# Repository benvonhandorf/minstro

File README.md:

# minstro
Remote control head for SDRs using the SoapyRemote server

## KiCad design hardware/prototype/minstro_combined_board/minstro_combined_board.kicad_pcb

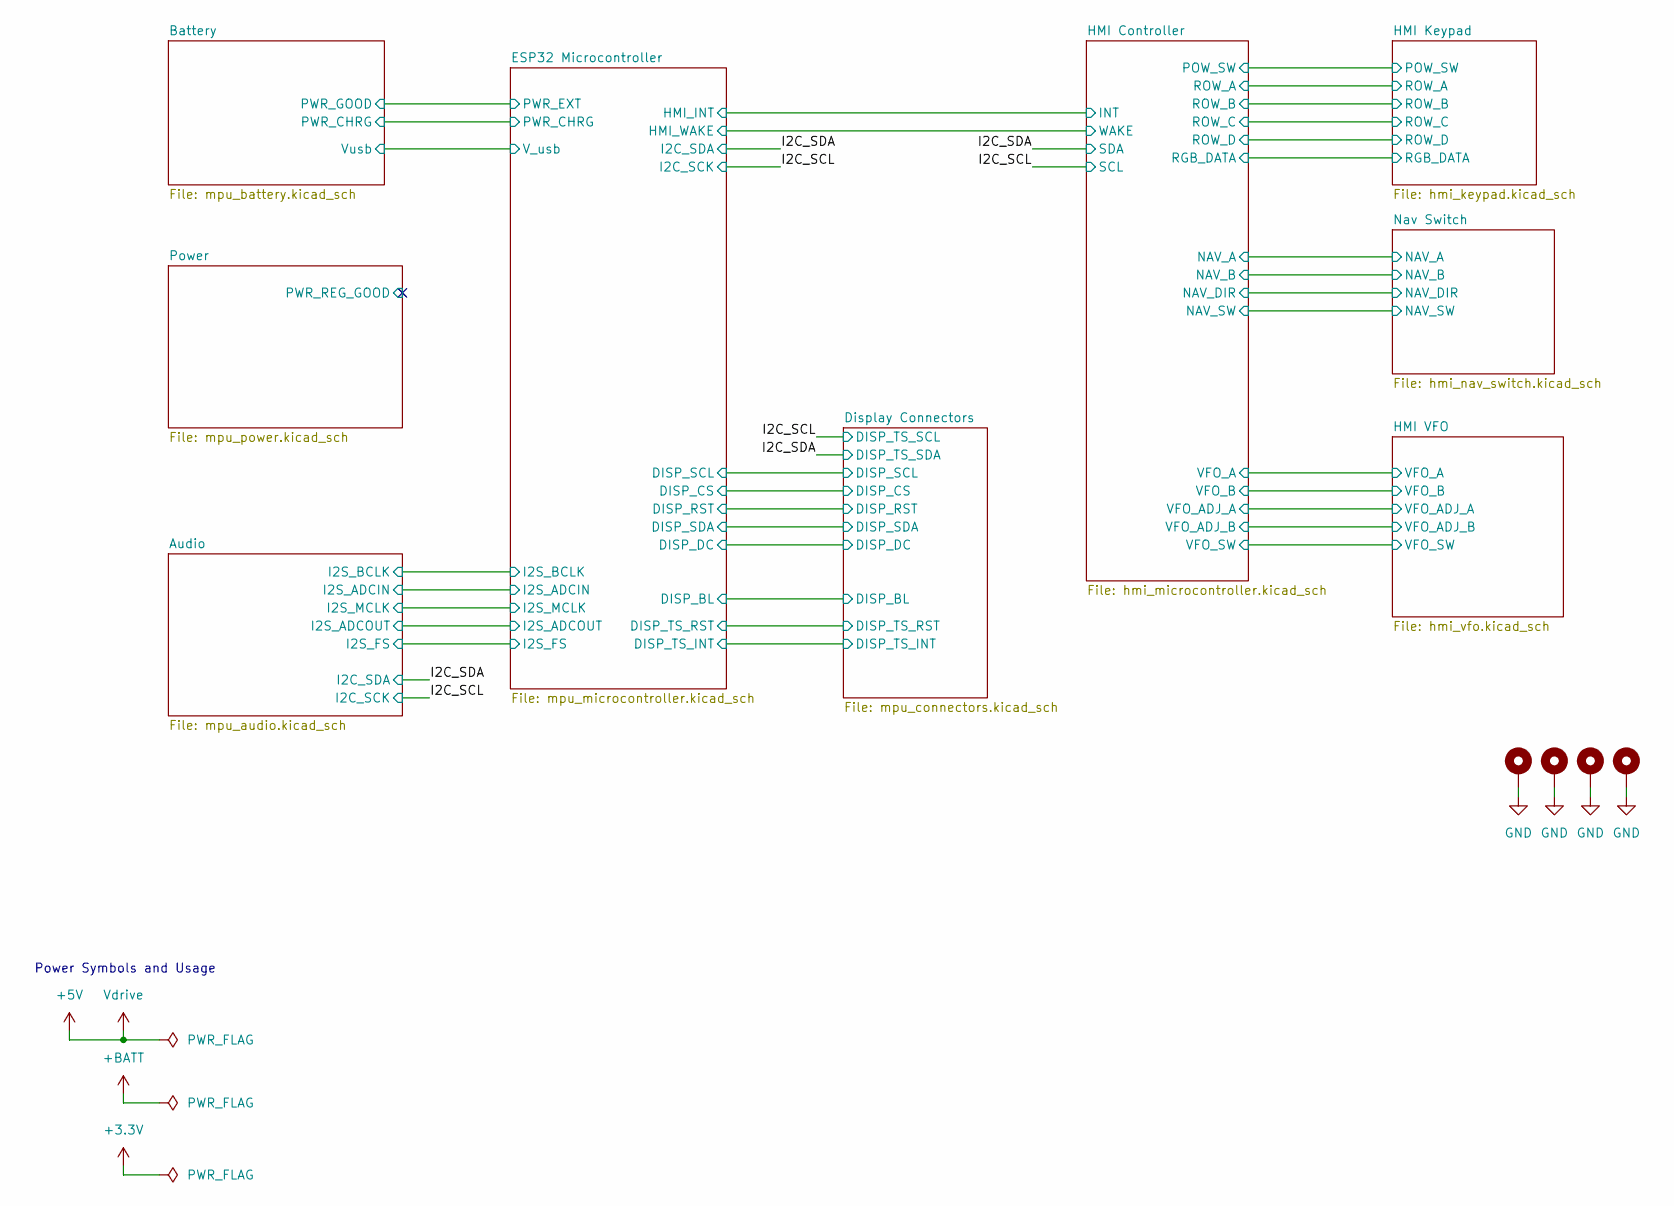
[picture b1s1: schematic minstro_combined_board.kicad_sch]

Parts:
H101, H102, H103, H104: MountingHole_Pad_MP; MountingHole_3.2mm_M3_Pad

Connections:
GND: H101.1, H102.1, H103.1, H104.1; also elsewhere on the board

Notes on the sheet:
Power Symbols and Usage

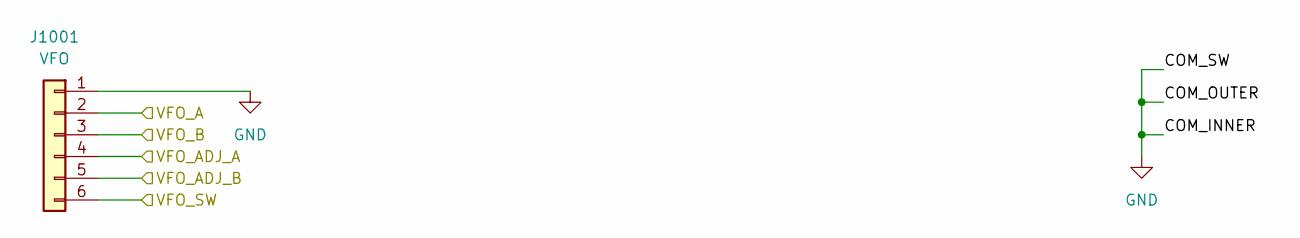
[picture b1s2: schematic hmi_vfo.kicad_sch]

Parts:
J1001: VFO; PinHeader_1x06_P2.54mm_Vertical

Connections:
/HMI Controller/VFO_A: J1001.2; also elsewhere on the board
/HMI Controller/VFO_ADJ_A: J1001.4; also elsewhere on the board
/HMI Controller/VFO_ADJ_B: J1001.5; also elsewhere on the board
/HMI Controller/VFO_B: J1001.3; also elsewhere on the board
/HMI Controller/VFO_SW: J1001.6; also elsewhere on the board
GND: J1001.1; also elsewhere on the board

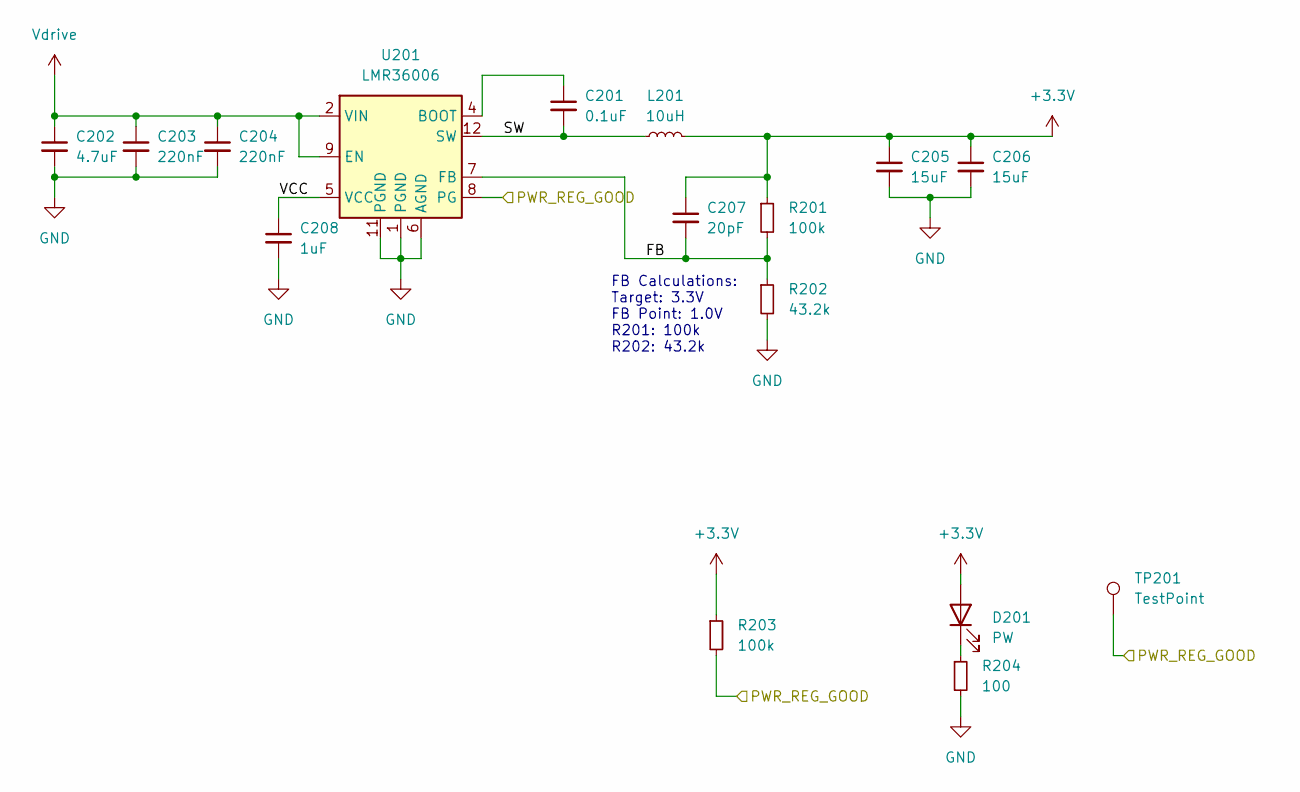
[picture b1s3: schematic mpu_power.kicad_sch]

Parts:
C201: 0.1uF; C_1206_3216Metric
C202: 4.7uF; C_1206_3216Metric
C203, C204: 220nF; C_1206_3216Metric
C205, C206: 15uF; C_1206_3216Metric
C207: 20pF; C_0805_2012Metric
C208: 1uF; C_0805_2012Metric
D201: PW; LED_0805_2012Metric
L201: 10uH; L_Taiyo-Yuden_MD-4040
R201, R203: 100k; R_0603_1608Metric
R202: 43.2k; R_0603_1608Metric
R204: 100; R_0603_1608Metric
TP201: TestPoint; TestPoint_Pad_D1.5mm
U201: LMR36006; LMR36006-VQFN-HR

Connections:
+3.3V: C205.1, C206.1, C207.1, D201.2 (A), L201.2, R201.1, R203.1; also elsewhere on the board
/Power/FB: C207.2, R201.2, R202.1, U201.7 (FB)
/Power/PWR_REG_GOOD: R203.2, TP201.1, U201.8 (PG)
/Power/SW: C201.2, L201.1, U201.3 (SW), U201.12 (SW)
/Power/VCC: C208.1, U201.5 (VCC)
GND: C202.2, C203.2, C204.2, C205.2, C206.2, C208.2, R202.2, R204.2, U201.1 (PGND), U201.6 (AGND), U201.11 (PGND); also elsewhere on the board
unnamed: D201.1 (K), R204.1
unnamed: C201.1, U201.4 (BOOT)

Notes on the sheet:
FB Calculations: Target: 3.3V FB Point: 1.0V R201: 100k R202: 43.2k

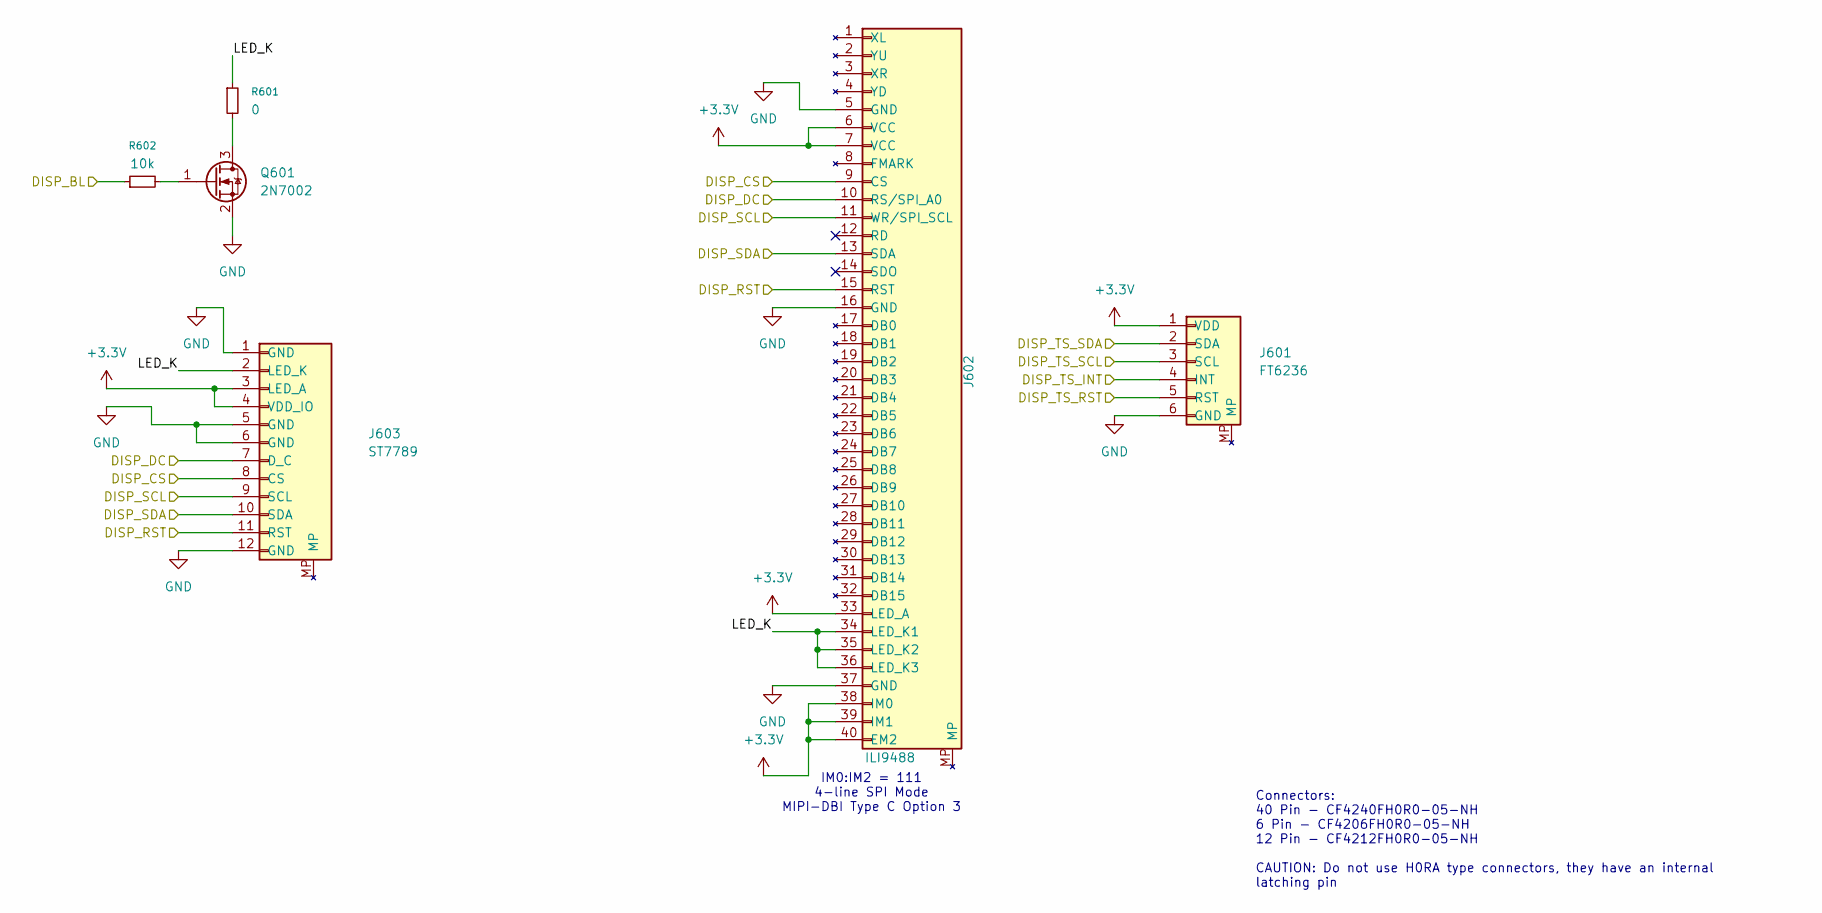
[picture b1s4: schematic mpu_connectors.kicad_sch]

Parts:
J601: FT6236; Cvilux_CF4206FH0R0-05-NH_FFC_01x06-1MP_P0.5mm_Horizontal
J602: ILI9488; Cvilux_CF4240FH0R0-05-NH_FFC_01x40-1MP_P0.5mm_Horizontal
J603: ST7789; Cvilux_CF4212FH0R0-05-NH_FFC_01x12-1MP_P0.5mm_Horizontal_1
Q601: 2N7002; SOT-23
R601: 0; R_0603_1608Metric_Pad0.98x0.95mm_HandSolder
R602: 10k; R_0603_1608Metric_Pad0.98x0.95mm_HandSolder

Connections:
+3.3V: J601.1 (VDD), J602.6 (VCC), J602.7 (VCC), J602.33 (LED_A), J602.38 (IM0), J602.39 (IM1), J602.40 (EM2), J603.3 (LED_A), J603.4 (VDD_IO); also elsewhere on the board
/Display Connectors/DISP_BL: R602.1; also elsewhere on the board
/Display Connectors/DISP_CS: J602.9 (CS), J603.8 (CS); also elsewhere on the board
/Display Connectors/DISP_DC: J602.10 (RS/SPI_A0), J603.7 (D_C); also elsewhere on the board
/Display Connectors/DISP_RST: J602.15 (RST), J603.11 (RST); also elsewhere on the board
/Display Connectors/DISP_SCL: J602.11 (WR/SPI_SCL), J603.9 (SCL); also elsewhere on the board
/Display Connectors/DISP_SDA: J602.13 (SDA), J603.10 (SDA); also elsewhere on the board
/Display Connectors/DISP_TS_INT: J601.4 (INT); also elsewhere on the board
/Display Connectors/DISP_TS_RST: J601.5 (RST); also elsewhere on the board
/Display Connectors/LED_K: J602.34 (LED_K1), J602.35 (LED_K2), J602.36 (LED_K3), J603.2 (LED_K), R601.1
/I2C_SCL: J601.3 (SCL); also elsewhere on the board
/I2C_SDA: J601.2 (SDA); also elsewhere on the board
GND: J601.6 (GND), J602.5 (GND), J602.16 (GND), J602.37 (GND), J603.1 (GND), J603.5 (GND), J603.6 (GND), J603.12 (GND), Q601.2 (S); also elsewhere on the board
unnamed: Q601.3 (D), R601.2
unnamed: Q601.1 (G), R602.2

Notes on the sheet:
IM0:IM2 = 111 4-line SPI Mode MIPI-DBI Type C Option 3
Connectors: 40 Pin - CF4240FH0R0-05-NH 6 Pin - CF4206FH0R0-05-NH 12 Pin - CF4212FH0R0-05-NH CAUTION: Do not use H0RA type connectors, they have an internal latching pin

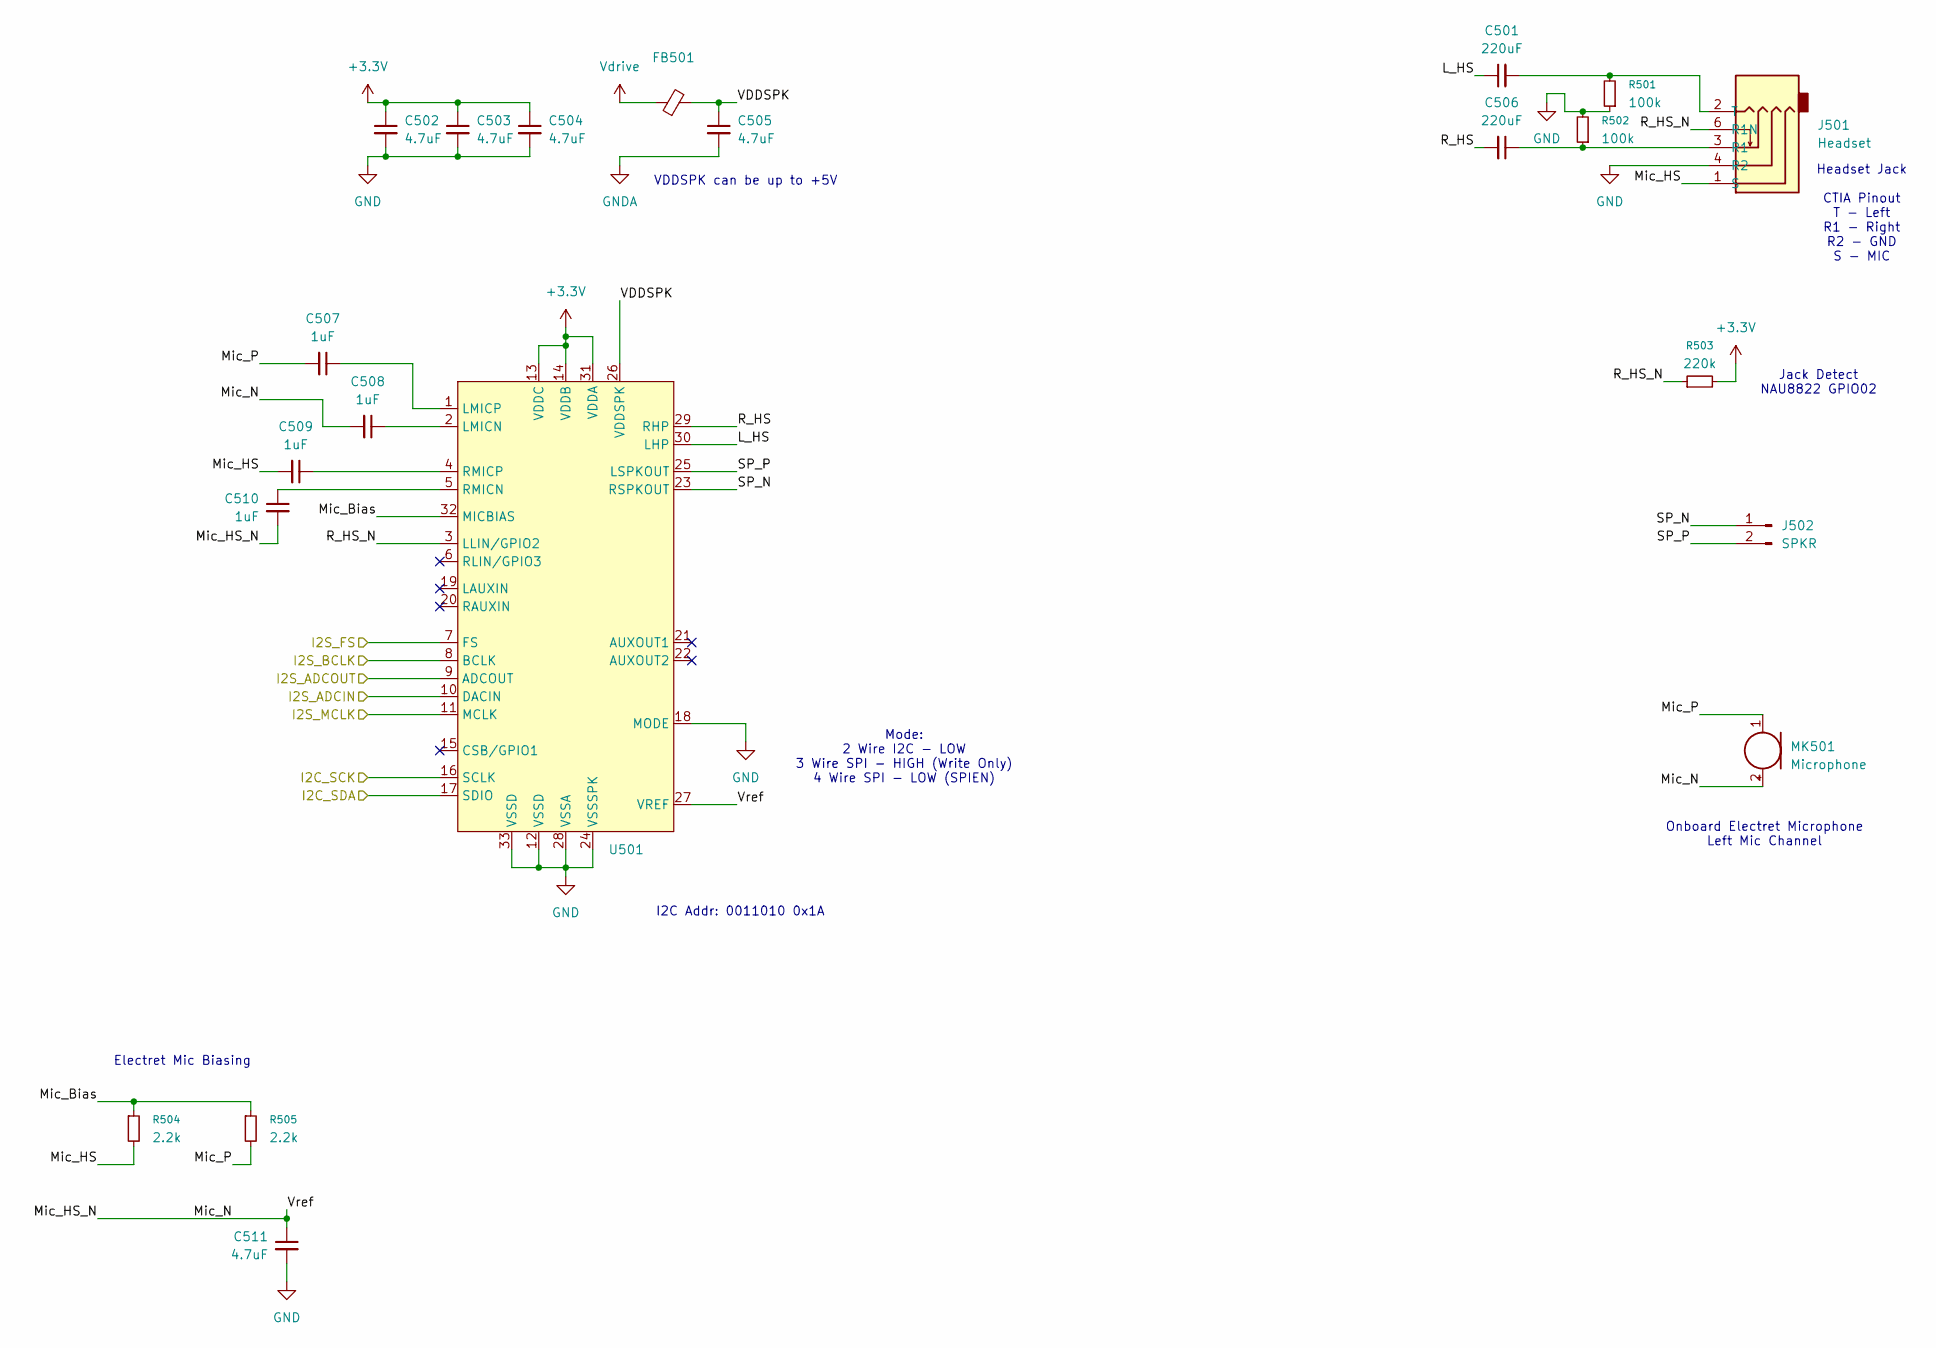
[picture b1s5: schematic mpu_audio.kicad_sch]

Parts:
C501, C506: 220uF; C_1210_3225Metric
C502, C503, C504, C505, C511: 4.7uF; C_0805_2012Metric
C507, C508, C509, C510: 1uF; C_0603_1608Metric
FB501: FerriteBead_Small; R_0805_2012Metric
J501: Headset; SJ-43515RS-SMT-TR
J502: SPKR; JST_ZH_B2B-ZR_1x02_P1.50mm_Vertical
MK501: Microphone; SameSky_CMB-6544PF_Electret_Mic_9.4d
R501, R502: 100k; R_0603_1608Metric
R503: 220k; R_0603_1608Metric
R504, R505: 2.2k; R_0603_1608Metric
U501: QFN-32-1EP_5x5mm_P0.5mm_EP2.7x2.7mm_ThermalVias

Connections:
+3.3V: C502.1, C503.1, C504.1, R503.2, U501.13 (VDDC), U501.14 (VDDB), U501.31 (VDDA); also elsewhere on the board
/Audio/I2S_ADCIN: U501.10 (DACIN); also elsewhere on the board
/Audio/I2S_ADCOUT: U501.9 (ADCOUT); also elsewhere on the board
/Audio/I2S_BCLK: U501.8 (BCLK); also elsewhere on the board
/Audio/I2S_FS: U501.7 (FS); also elsewhere on the board
/Audio/I2S_MCLK: U501.11 (MCLK); also elsewhere on the board
/Audio/L_HS: C501.1, U501.30 (LHP)
/Audio/Mic_Bias: R504.1, R505.1, U501.32 (MICBIAS)
/Audio/Mic_HS: C509.2, J501.1 (S), R504.2
/Audio/Mic_HS_N: C508.2, C510.2, C511.1, MK501.2 (+), U501.27 (VREF)
/Audio/Mic_P: C507.2, MK501.1 (-), R505.2
/Audio/R_HS: C506.2, U501.29 (RHP)
/Audio/R_HS_N: J501.6 (R1N), R503.1, U501.3 (LLIN/GPIO2)
/Audio/SP_N: J502.1, U501.23 (RSPKOUT)
/Audio/SP_P: J502.2, U501.25 (LSPKOUT)
/Audio/VDDSPK: C505.1, FB501.2, U501.26 (VDDSPK)
/I2C_SCL: U501.16 (SCLK); also elsewhere on the board
/I2C_SDA: U501.17 (SDIO); also elsewhere on the board
GND: C502.2, C503.2, C504.2, C511.2, J501.4 (R2), R501.1, R502.2, U501.12 (VSSD), U501.18 (MODE), U501.24 (VSSSPK), U501.28 (VSSA), U501.33 (VSSD); also elsewhere on the board
GNDA: C505.2
unnamed: C506.1, J501.3 (R1), R502.1
unnamed: C501.2, J501.2 (T), R501.2
unnamed: C508.1, U501.2 (LMICN)
unnamed: C507.1, U501.1 (LMICP)
unnamed: C510.1, U501.5 (RMICN)
unnamed: C509.1, U501.4 (RMICP)

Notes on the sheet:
Onboard Electret Microphone Left Mic Channel
VDDSPK can be up to +5V
Electret Mic Biasing
I2C Addr: 0011010 0x1A
Mode: 2 Wire I2C - LOW 3 Wire SPI - HIGH (Write Only) 4 Wire SPI - LOW (SPIEN)
Headset Jack CTIA Pinout T - Left R1 - Right R2 - GND S - MIC
Jack Detect NAU8822 GPIO02

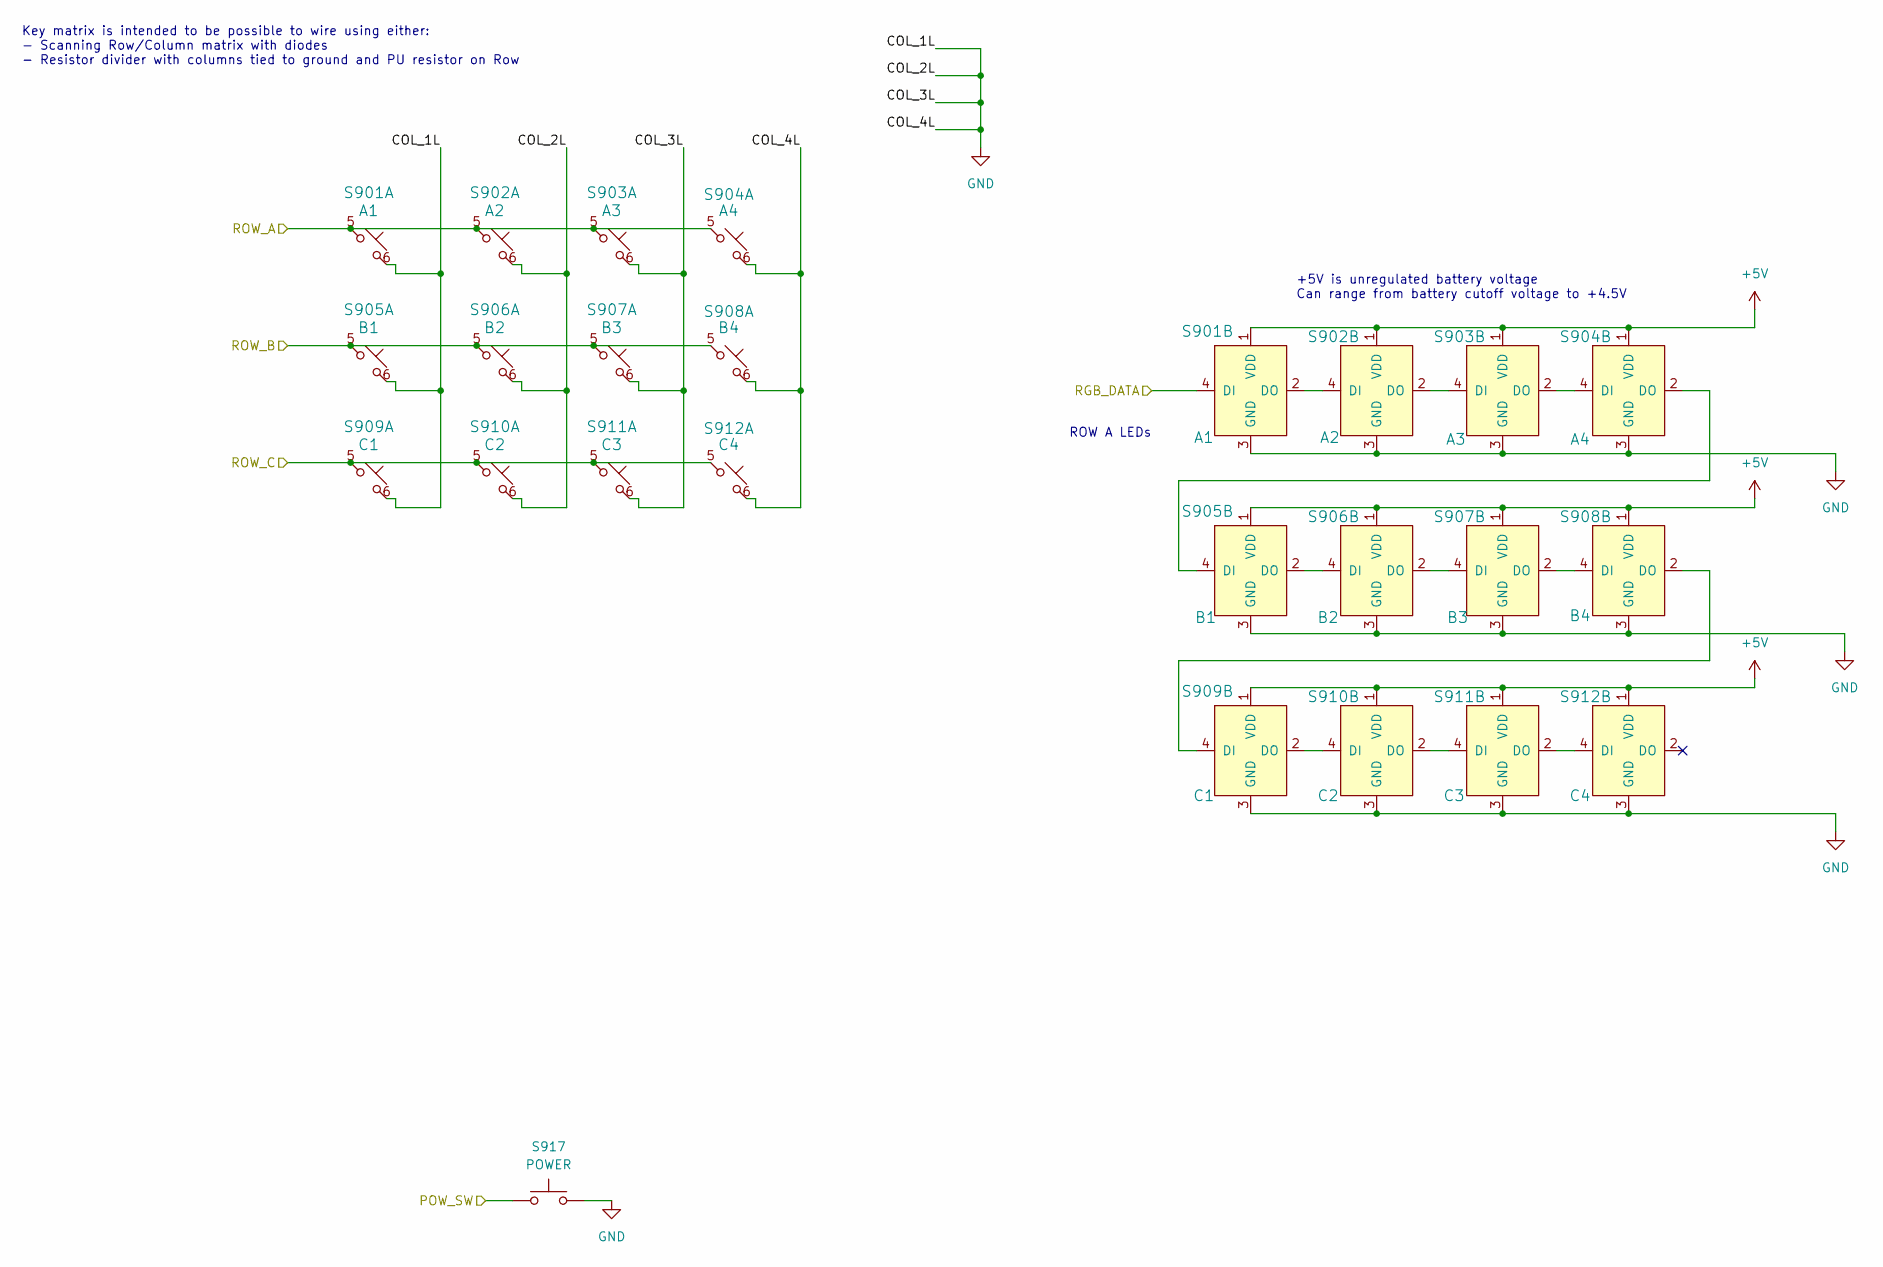
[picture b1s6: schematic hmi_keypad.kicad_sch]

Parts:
S901: A1; TacButton_6mm_6mm_SK6812-E-Mini
S902: A2; TacButton_6mm_6mm_SK6812-E-Mini
S903: A3; TacButton_6mm_6mm_SK6812-E-Mini
S904: A4; TacButton_6mm_6mm_SK6812-E-Mini
S905: B1; TacButton_6mm_6mm_SK6812-E-Mini
S906: B2; TacButton_6mm_6mm_SK6812-E-Mini
S907: B3; TacButton_6mm_6mm_SK6812-E-Mini
S908: B4; TacButton_6mm_6mm_SK6812-E-Mini
S909: C1; TacButton_6mm_6mm_SK6812-E-Mini
S910: C2; TacButton_6mm_6mm_SK6812-E-Mini
S911: C3; TacButton_6mm_6mm_SK6812-E-Mini
S912: C4; TacButton_6mm_6mm_SK6812-E-Mini
S917: POWER; Tac_SPST_RightAngle_SideActuated_THT

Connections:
/HMI Controller/POW_SW: S917.1; also elsewhere on the board
/HMI Controller/RGB_DATA: S901.4 (DI); also elsewhere on the board
/HMI Controller/ROW_A: S901.5, S902.5, S903.5, S904.5; also elsewhere on the board
/HMI Controller/ROW_B: S905.5, S906.5, S907.5, S908.5; also elsewhere on the board
/HMI Controller/ROW_C: S909.5, S910.5, S911.5, S912.5; also elsewhere on the board
GND: S901.3 (GND), S901.6, S902.3 (GND), S902.6, S903.3 (GND), S903.6, S904.3 (GND), S904.6, S905.3 (GND), S905.6, S906.3 (GND), S906.6, S907.3 (GND), S907.6, S908.3 (GND), S908.6, S909.3 (GND), S909.6, S910.3 (GND), S910.6, S911.3 (GND), S911.6, S912.3 (GND), S912.6, S917.2; also elsewhere on the board
unnamed: S901.2 (DO), S902.4 (DI)
unnamed: S902.2 (DO), S903.4 (DI)
unnamed: S903.2 (DO), S904.4 (DI)
unnamed: S904.2 (DO), S905.4 (DI)
unnamed: S905.2 (DO), S906.4 (DI)
unnamed: S906.2 (DO), S907.4 (DI)
unnamed: S907.2 (DO), S908.4 (DI)
unnamed: S908.2 (DO), S909.4 (DI)
unnamed: S909.2 (DO), S910.4 (DI)
unnamed: S910.2 (DO), S911.4 (DI)
unnamed: S911.2 (DO), S912.4 (DI)

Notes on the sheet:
+5V is unregulated battery voltage Can range from battery cutoff voltage to +4.5V
Key matrix is intended to be possible to wire using either: - Scanning Row/Column matrix with diodes - Resistor divider with columns tied to ground and PU resistor on Row
ROW A LEDs

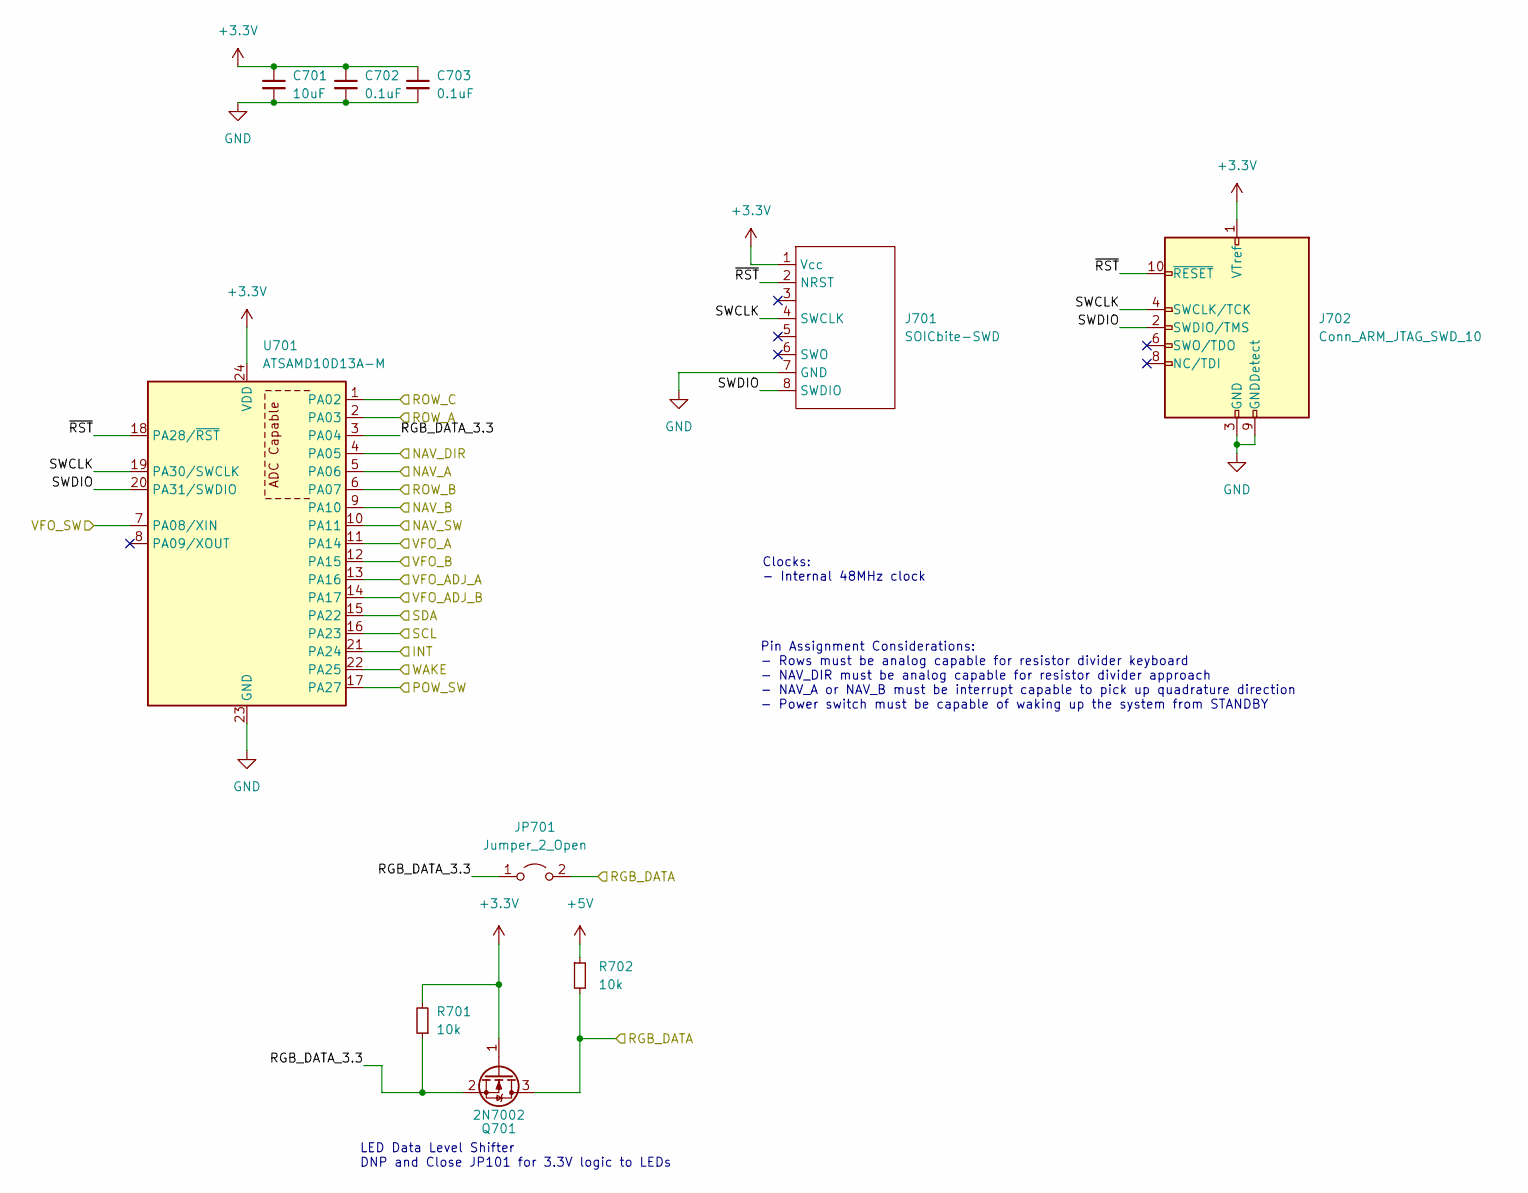
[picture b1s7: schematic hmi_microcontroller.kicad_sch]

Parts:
C701: 10uF; C_0805_2012Metric
C702, C703: 0.1uF; C_0603_1608Metric
J701: SOICbite-SWD; SOICbite_renumbered
J702: Conn_ARM_JTAG_SWD_10; Cortex_Debug_PinSocket_2x05_P1.27mm_Vertical_SMD
JP701: Jumper_2_Open; SolderJumper-2_P1.3mm_Open_Pad1.0x1.5mm
Q701: 2N7002; SOT-23
R701, R702: 10k; R_0805_2012Metric_Pad1.20x1.40mm_HandSolder
U701: ATSAMD10D13A-M; QFN-24-1EP_4x4mm_P0.5mm_EP2.6x2.6mm_ThermalVias

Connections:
+3.3V: C701.1, C702.1, C703.1, J701.1 (Vcc), J702.1 (VTref), Q701.1 (G), R701.2, U701.24 (VDD); also elsewhere on the board
/ESP32 Microcontroller/HMI_INT: U701.21 (PA24); also elsewhere on the board
/ESP32 Microcontroller/HMI_WAKE: U701.22 (PA25); also elsewhere on the board
/HMI Controller/NAV_A: U701.5 (PA06); also elsewhere on the board
/HMI Controller/NAV_B: U701.9 (PA10); also elsewhere on the board
/HMI Controller/NAV_DIR: U701.4 (PA05); also elsewhere on the board
/HMI Controller/NAV_SW: U701.10 (PA11); also elsewhere on the board
/HMI Controller/POW_SW: U701.17 (PA27); also elsewhere on the board
/HMI Controller/RGB_DATA: JP701.2 (B), Q701.3 (D), R702.2; also elsewhere on the board
/HMI Controller/RGB_DATA_3.3: JP701.1 (A), Q701.2 (S), R701.1, U701.3 (PA04)
/HMI Controller/ROW_A: U701.2 (PA03); also elsewhere on the board
/HMI Controller/ROW_B: U701.6 (PA07); also elsewhere on the board
/HMI Controller/ROW_C: U701.1 (PA02); also elsewhere on the board
/HMI Controller/SWCLK: J701.4 (SWCLK), J702.4 (SWCLK/TCK), U701.19 (PA30/SWCLK)
/HMI Controller/SWDIO: J701.8 (SWDIO), J702.2 (SWDIO/TMS), U701.20 (PA31/SWDIO)
/HMI Controller/VFO_A: U701.11 (PA14); also elsewhere on the board
/HMI Controller/VFO_ADJ_A: U701.13 (PA16); also elsewhere on the board
/HMI Controller/VFO_ADJ_B: U701.14 (PA17); also elsewhere on the board
/HMI Controller/VFO_B: U701.12 (PA15); also elsewhere on the board
/HMI Controller/VFO_SW: U701.7 (PA08/XIN); also elsewhere on the board
/HMI Controller/~RST: J701.2 (NRST), J702.10 (~RESET), U701.18 (PA28/~RST)
/I2C_SCL: U701.16 (PA23); also elsewhere on the board
/I2C_SDA: U701.15 (PA22); also elsewhere on the board
GND: C701.2, C702.2, C703.2, J701.7 (GND), J702.3 (GND), J702.5 (GND), J702.9 (GNDDetect), U701.23 (GND), U701.25 (GND); also elsewhere on the board

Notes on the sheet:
Clocks: - Internal 48MHz clock
LED Data Level Shifter DNP and Close JP101 for 3.3V logic to LEDs
Pin Assignment Considerations: - Rows must be analog capable for resistor divider keyboard - NAV_DIR must be analog capable for resistor divider approach - NAV_A or NAV_B must be interrupt capable to pick up quadrature direction - Power switch must be capable of waking up the system from STANDBY

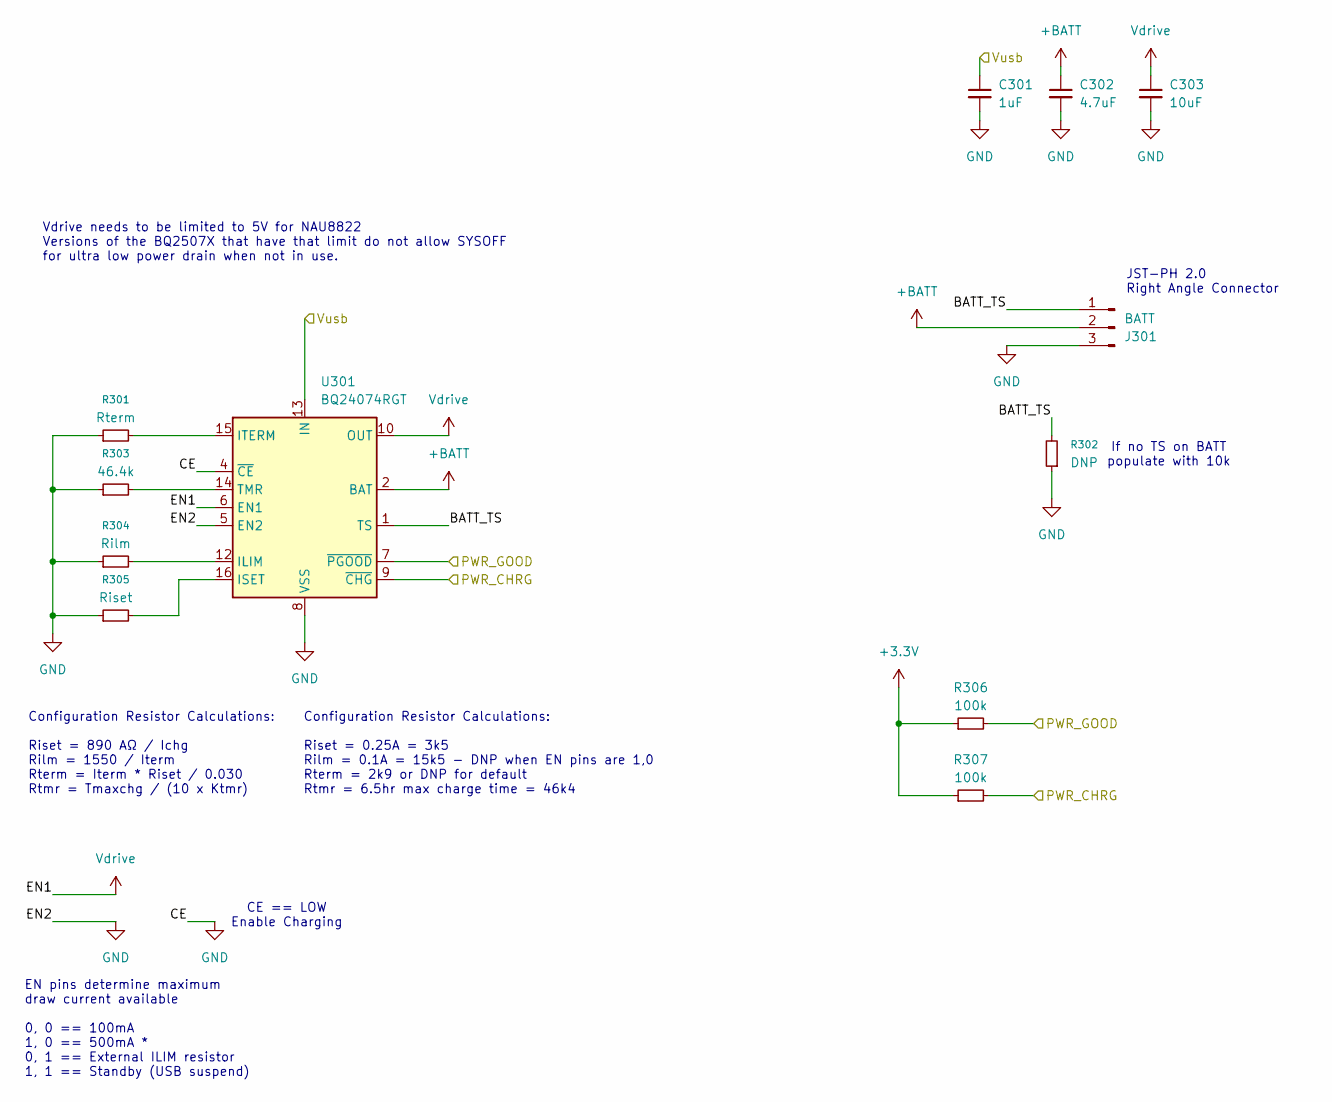
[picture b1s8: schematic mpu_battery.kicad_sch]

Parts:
C301: 1uF; C_1206_3216Metric
C302: 4.7uF; C_1206_3216Metric
C303: 10uF; C_1206_3216Metric
J301: BATT; JST_PH_S3B-PH-K_1x03_P2.00mm_Horizontal
R301: Rterm; R_0603_1608Metric
R302: DNP; R_0603_1608Metric
R303: 46.4k; R_0603_1608Metric
R304: Rilm; R_0603_1608Metric
R305: Riset; R_0603_1608Metric
R306, R307: 100k; R_0603_1608Metric
U301: BQ24074RGT; VQFN-16-1EP_3x3mm_P0.5mm_EP1.6x1.6mm_ThermalVias

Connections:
+3.3V: R306.1, R307.1; also elsewhere on the board
+BATT: C302.1, J301.2, U301.2 (BAT), U301.3 (BAT)
/Battery/BATT_TS: J301.1, R302.2, U301.1 (TS)
/Battery/PWR_CHRG: R307.2, U301.9 (~CHG); also elsewhere on the board
/Battery/PWR_GOOD: R306.2, U301.7 (~PGOOD); also elsewhere on the board
/Battery/Vusb: C301.1, U301.13 (IN); also elsewhere on the board
GND: C301.2, C302.2, C303.2, J301.3, R301.1, R302.1, R303.1, R304.1, R305.1, U301.4 (~CE), U301.5 (EN2), U301.8 (VSS), U301.17 (VSS); also elsewhere on the board
unnamed: R304.2, U301.12 (ILIM)
unnamed: R305.2, U301.16 (ISET)
unnamed: R301.2, U301.15 (ITERM)
unnamed: R303.2, U301.14 (TMR)

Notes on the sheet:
Configuration Resistor Calculations: Riset = 0.25A = 3k5 Rilm = 0.1A = 15k5 - DNP when EN pins are 1,0 Rterm = 2k9 or DNP for default Rtmr = 6.5hr max charge time = 46k4
JST-PH 2.0 Right Angle Connector
EN pins determine maximum draw current available 0, 0 == 100mA 1, 0 == 500mA * 0, 1 == External ILIM resistor 1, 1 == Standby (USB suspend)
Vdrive needs to be limited to 5V for NAU8822 Versions of the BQ2507X that have that limit do not allow SYSOFF for ultra low power drain when not in use.
If no TS on BATT populate with 10k
Configuration Resistor Calculations: Riset = 890 AΩ / Ichg Rilm = 1550 / Iterm Rterm = Iterm * Riset / 0.030 Rtmr = Tmaxchg / (10 x Ktmr)
CE == LOW Enable Charging
